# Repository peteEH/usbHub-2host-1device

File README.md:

# usbHub-2host-1device
Single Device can be switched between two hosts

## LICENSE ##
Hardware License is Creative Commons - Attribution 3.0

Feel free to use these files to learn, explore electronics.

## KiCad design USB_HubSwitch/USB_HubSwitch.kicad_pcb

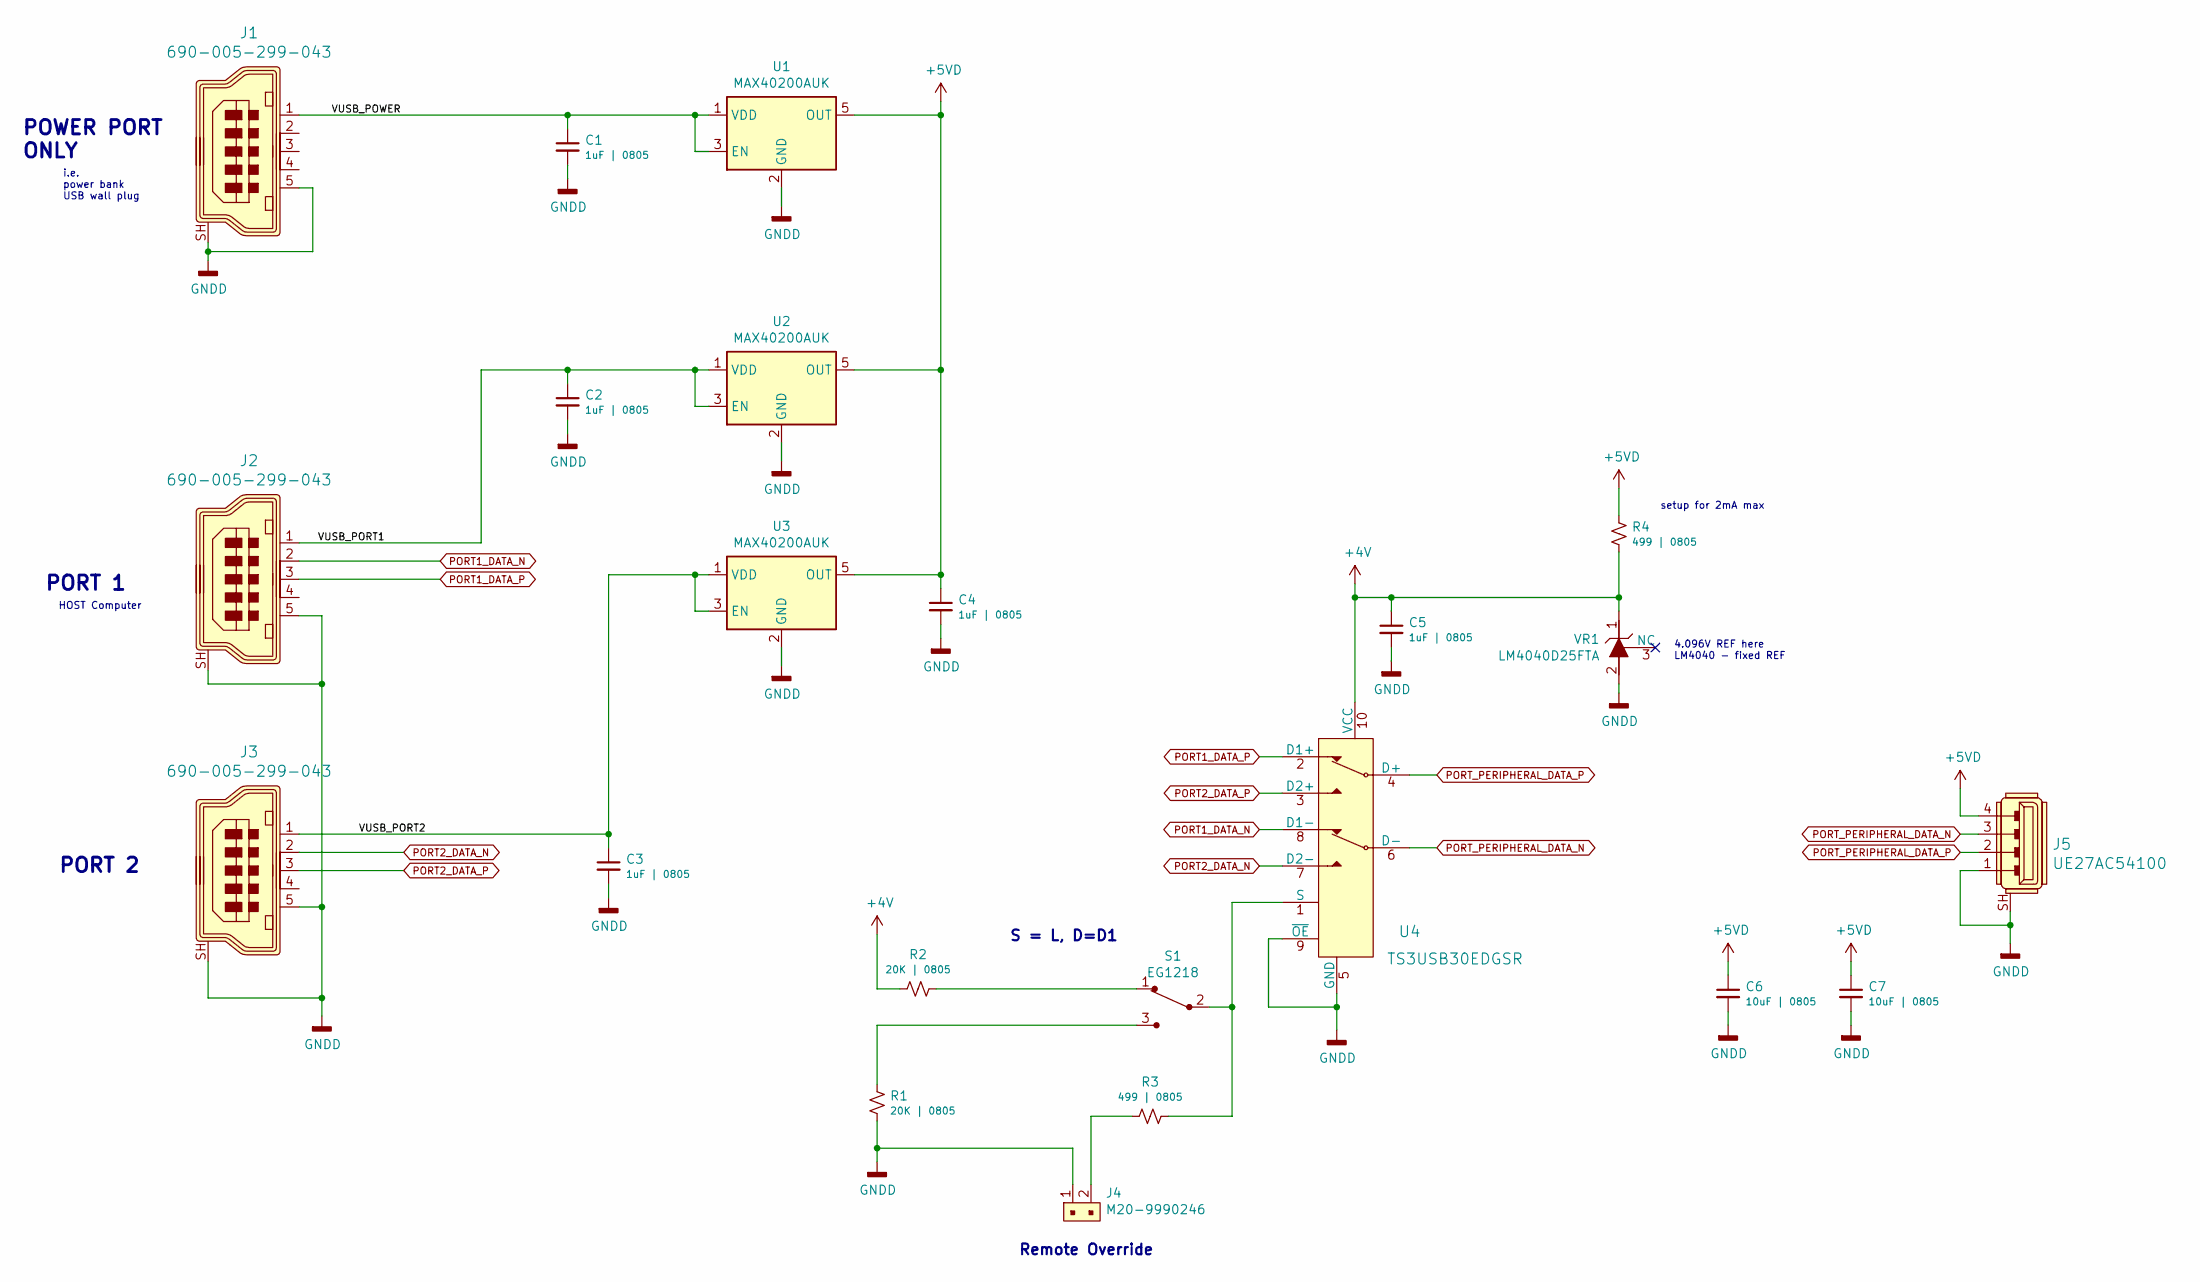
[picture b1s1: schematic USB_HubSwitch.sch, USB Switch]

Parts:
C1, C2, C3, C4, C5: 1uF | 0805; C_0805_2012Metric
C6, C7: 10uF | 0805; C_0805_2012Metric
J1, J2, J3: 690-005-299-043; USB_Mini_B_Female_690-005-299-043; MPN 690-005-299-043; Digi-Key_PN 151-1206-1-ND
J4: M20-9990246; PinHeader_1x2_P2.54mm; MPN M20-9990246; Digi-Key_PN 952-2262-ND
J5: UE27AC54100; USB_A_Female_UE27AC54100; MPN UE27AC54100; Digi-Key_PN UE27AC54100-ND
R1, R2: 20K | 0805; R_0805_2012Metric
R3, R4: 499 | 0805; R_0805_2012Metric
S1: EG1218; Switch_Slide_11.6x4mm_EG1218; MPN EG1218; Digi-Key_PN EG1903-ND
U1, U2, U3: MAX40200AUK; SOT-23-5
U4: TS3USB30EDGSR; MSOP-10_W3mm; MPN TS3USB30EDGSR; Digi-Key_PN 296-25495-1-ND
VR1: LM4040D25FTA; SOT-23-3; MPN LM4040D25FTA; Digi-Key_PN LM4040D25FCT-ND

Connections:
+4V: C5.1, R2.2, R4.2, U4.10 (VCC), VR1.1
+5VD: C4.1, C6.1, C7.1, J5.4, R4.1, U1.5 (OUT), U2.5 (OUT), U3.5 (OUT)
/VUSB_PORT1: C2.1, J2.1, U2.1 (VDD), U2.3 (EN)
/VUSB_PORT2: C3.1, J3.1, U3.1 (VDD), U3.3 (EN)
/VUSB_POWER: C1.1, J1.1, U1.1 (VDD), U1.3 (EN)
GNDD: C1.2, C2.2, C3.2, C4.2, C5.2, C6.2, C7.2, J1.5, J1.SH, J2.5, J2.SH, J3.5, J3.SH, J4.1, J5.1, J5.SH, R1.2, U1.2 (GND), U2.2 (GND), U3.2 (GND), U4.5 (GND), U4.9 (~OE), VR1.2
unnamed: J4.2, R3.2
unnamed: R1.1, S1.3
unnamed: R2.1, S1.1
unnamed: R3.1, S1.2, U4.1 (S)
PORT1_DATA_N: J2.2, U4.8 (D1-)
PORT1_DATA_P: J2.3, U4.2 (D1+)
PORT2_DATA_N: J3.2, U4.7 (D2-)
PORT2_DATA_P: J3.3, U4.3 (D2+)
PORT_PERIPHERAL_DATA_N: J5.3, U4.6 (D-)
PORT_PERIPHERAL_DATA_P: J5.2, U4.4 (D+)

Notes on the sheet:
4.096V REF here LM4040 - fixed REF
setup for 2mA max
PORT 1
PORT 2
POWER PORT ONLY
i.e. power bank USB wall plug
HOST Computer
Remote Override
S = L, D=D1

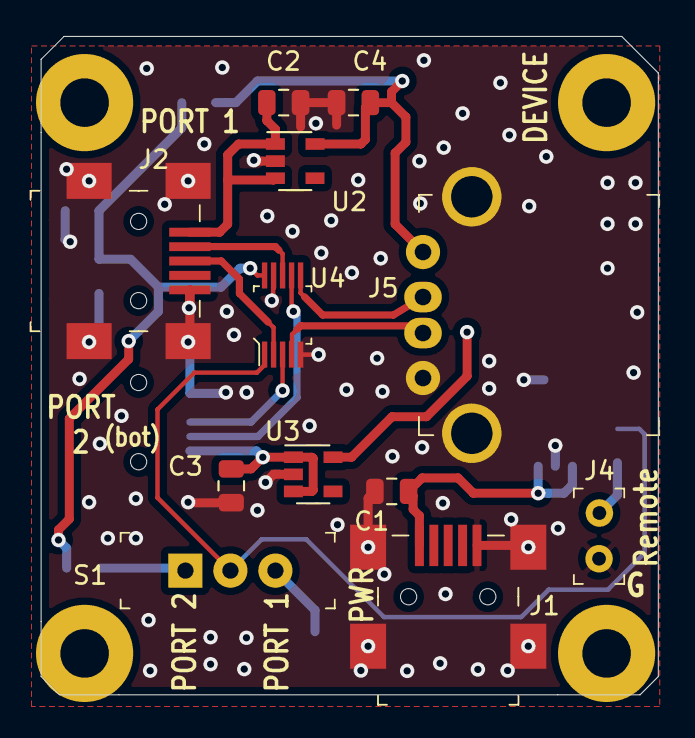
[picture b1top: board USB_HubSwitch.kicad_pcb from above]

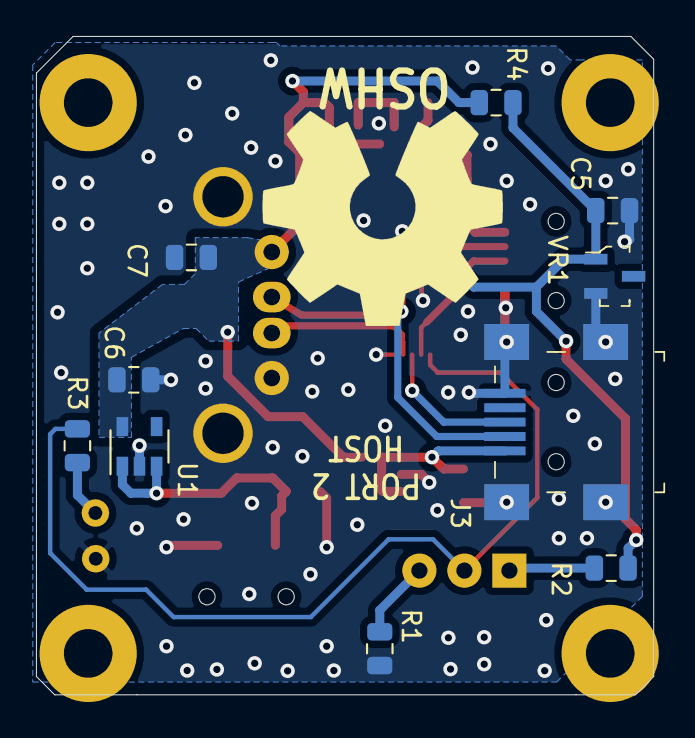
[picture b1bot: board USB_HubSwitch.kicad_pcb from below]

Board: 2 copper layers, 34.3 x 36.6 mm, 22 parts (10 on the bottom side), 16 nets.

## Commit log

2019-10-26 added initial set of design files
2019-10-26 Fixed USB Receptacle Pinout
    this shall be used... fixed TYPE A pinout, was flipped vertically
2019-10-26 incorrect usb pinout
2019-10-26 added license
